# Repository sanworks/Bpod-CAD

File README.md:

# Bpod-CAD
CAD files for the Bpod behavior measurement system.
Bills of materials and build tips are given on the Bpod Wiki: https://sites.google.com/site/bpoddocumentation/home

(C) 2023 Sanworks LLC. These files are freely available under the terms of General Public License v3.0 (enclosed with this repository).

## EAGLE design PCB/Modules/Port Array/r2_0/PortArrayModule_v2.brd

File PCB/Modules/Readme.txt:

Note: With the exception of the 'For FSM r0.5' folder, modules in this folder are compatible with state machine r0.7 or newer.

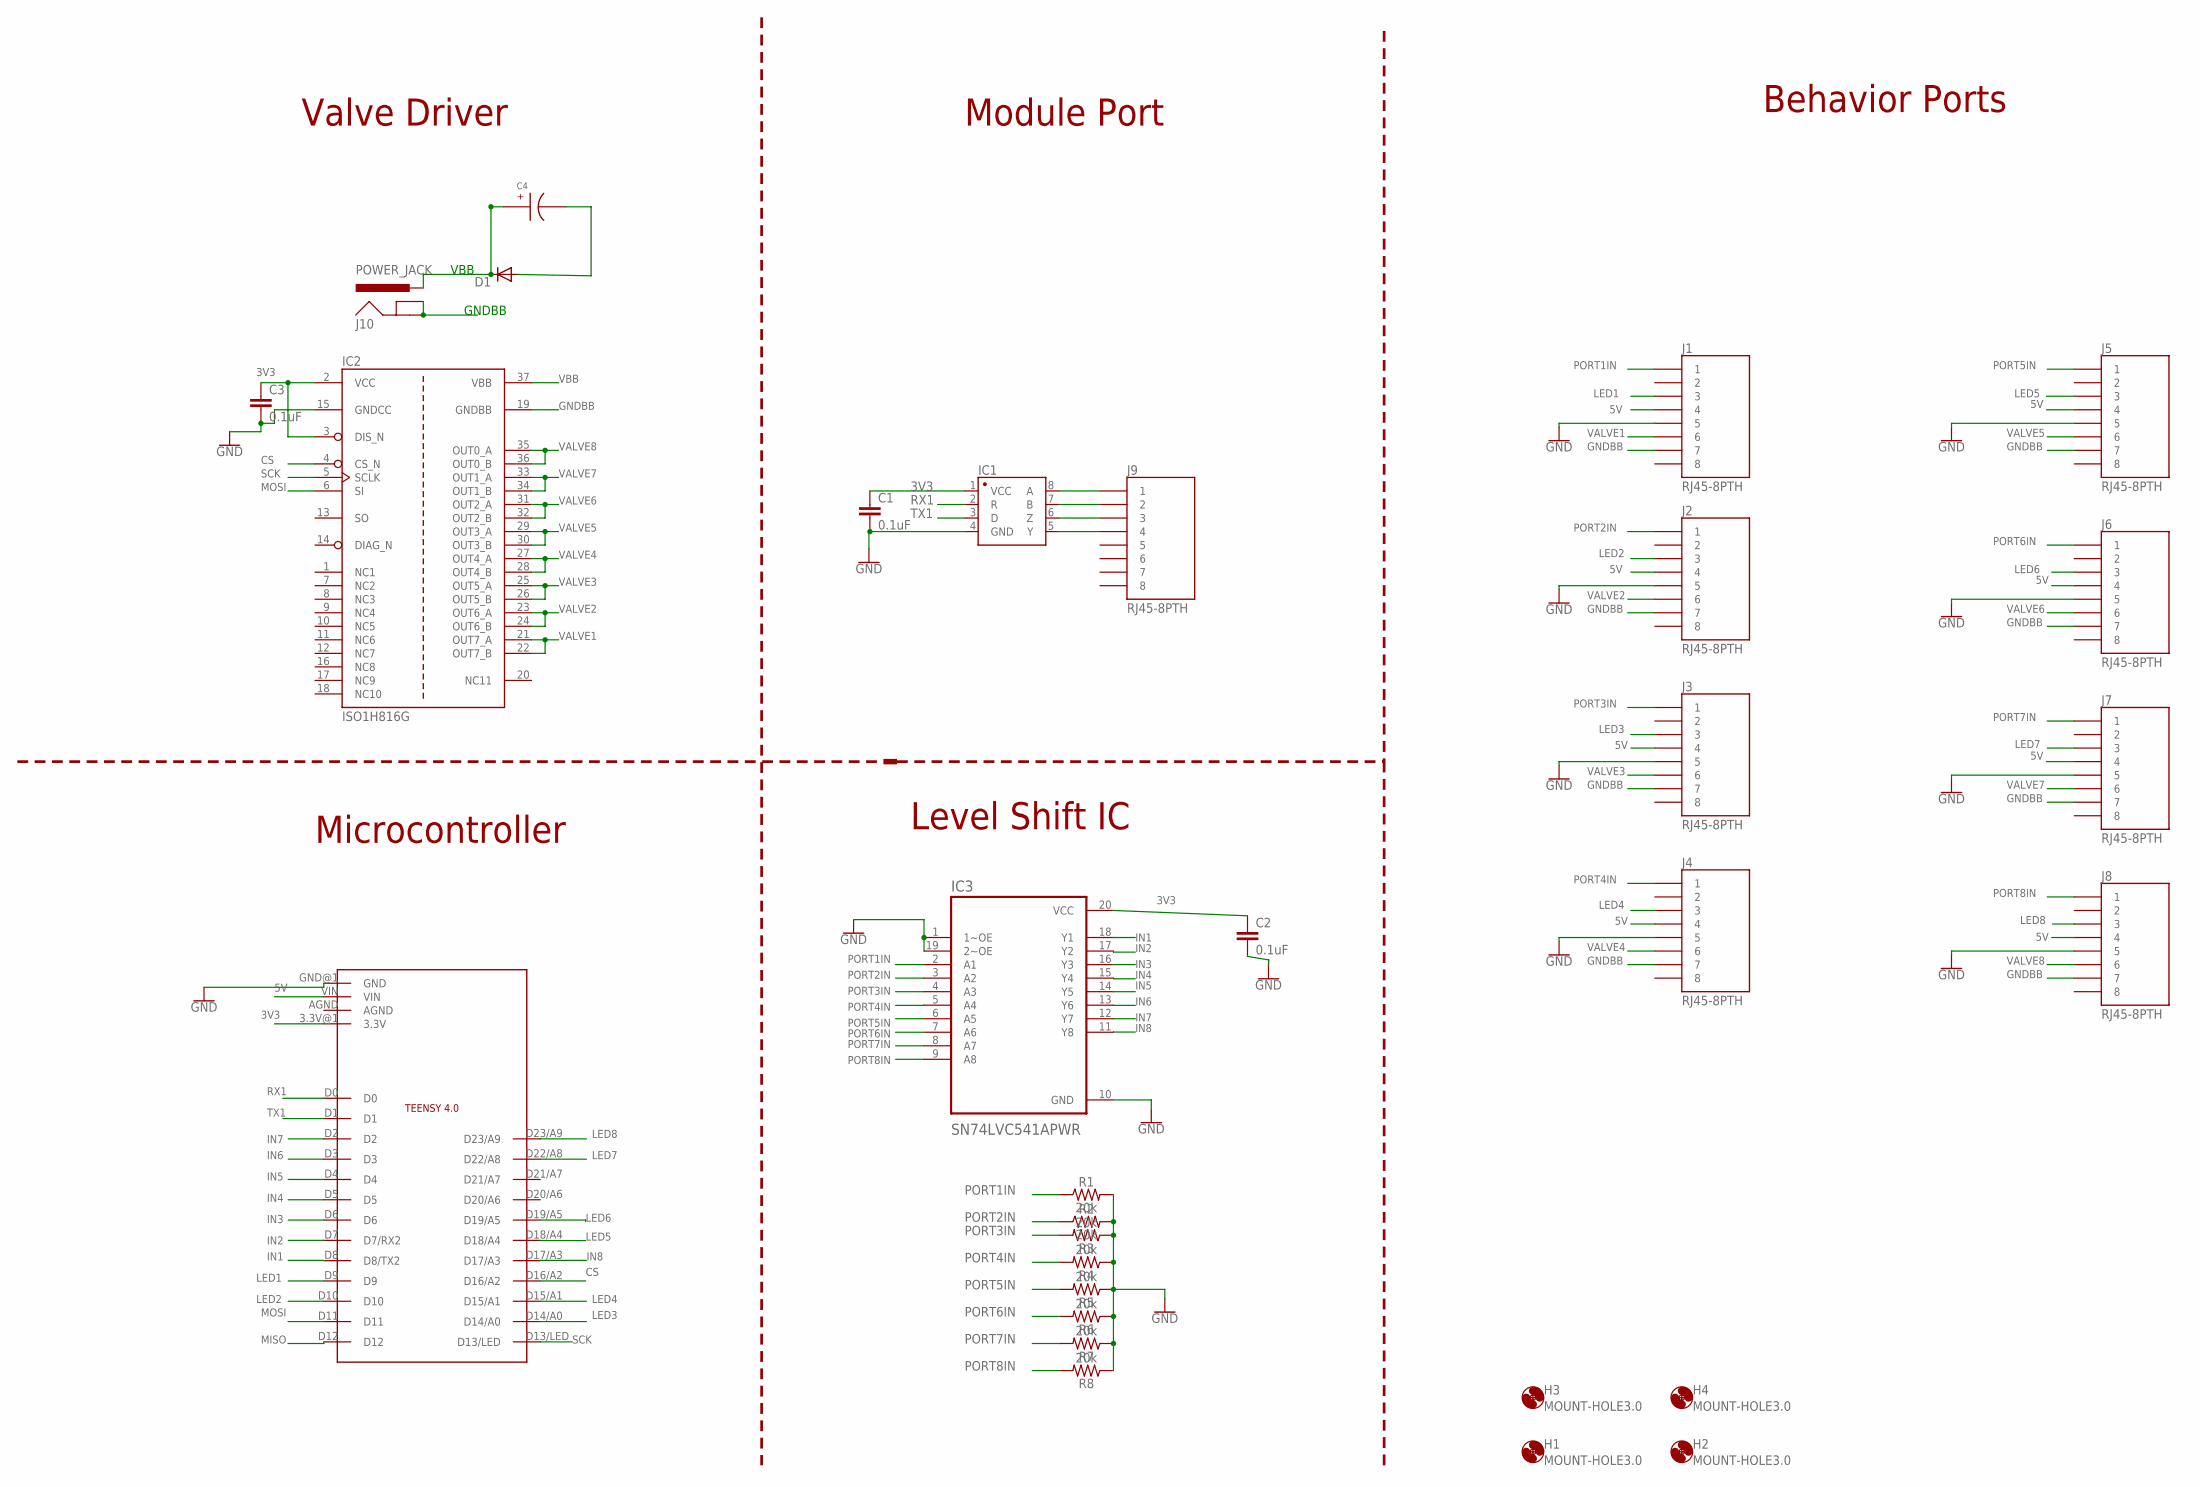
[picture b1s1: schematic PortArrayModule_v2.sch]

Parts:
C1, C2, C3: 0.1uF; 0805
C4: EEE-FK1H100UR
D1: DIODE-DO214AA; DO214AA
H1, H2, H3, H4: MOUNT-HOLE3.0; 3,0
IC1: SN65HVD31DR; SO08
IC2: ISO1H816G; SOP65P1420X350-37N-1-V
IC3: SN74LVC541APWR; SOP65P640X120-20N
J1, J2, J3, J4, J5, J6, J7, J8, J9: RJ45-8PTH; RJ45-8
J10: POWER_JACK; POWER_JACK_PTH
MC1: TEENSY4.0_SIMPLE_NO_VUSB
R1, R2, R3, R4, R5, R6, R7, R8: 20k; 0805

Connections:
3V3: C1.1, C2.1, C3.1, IC1.1 (VCC), IC2.2 (VCC), IC2.3 (DIS_N), IC3.20 (VCC), MC1.3.3V@1 (3.3V)
5V: J1.4, J2.4, J3.4, J4.4, J5.4, J6.4, J7.4, J8.4, MC1.VIN
CS: IC2.4 (CS_N), MC1.D16/A2
GND: C1.2, C2.2, C3.2, IC1.4 (GND), IC2.15 (GNDCC), IC3.1 (1~OE), IC3.10 (GND), IC3.19 (2~OE), J1.5, J2.5, J3.5, J4.5, J5.5, J6.5, J7.5, J8.5, MC1.GND@1 (GND), R1.2, R2.2, R3.1, R4.1, R5.1, R6.1, R7.1, R8.1
GNDBB: C4.CATHODE, D1.A, IC2.19 (GNDBB), J1.7, J2.7, J3.7, J4.7, J5.7, J6.7, J7.7, J8.7, J10.GND, J10.GNDBREAK
IN1: IC3.18 (Y1), MC1.D8 (D8/TX2)
IN2: IC3.17 (Y2), MC1.D7 (D7/RX2)
IN3: IC3.16 (Y3), MC1.D6
IN4: IC3.15 (Y4), MC1.D5
IN5: IC3.14 (Y5), MC1.D4
IN6: IC3.13 (Y6), MC1.D3
IN7: IC3.12 (Y7), MC1.D2
IN8: IC3.11 (Y8), MC1.D17/A3
LED1: J1.3, MC1.D9
LED2: J2.3, MC1.D10
LED3: J3.3, MC1.D14/A0
LED4: J4.3, MC1.D15/A1
LED5: J5.3, MC1.D18/A4
LED6: J6.3, MC1.D19/A5
LED7: J7.3, MC1.D22/A8
LED8: J8.3, MC1.D23/A9
MISO: MC1.D12
MOSI: IC2.6 (SI), MC1.D11
unnamed: IC1.6 (Z), J9.3
unnamed: IC1.5 (Y), J9.4
unnamed: IC1.8 (A), J9.1
unnamed: IC1.7 (B), J9.2
PORT1IN: IC3.2 (A1), J1.1, R1.1
PORT2IN: IC3.3 (A2), J2.1, R2.1
PORT3IN: IC3.4 (A3), J3.1, R3.2
PORT4IN: IC3.5 (A4), J4.1, R4.2
PORT5IN: IC3.6 (A5), J5.1, R5.2
PORT6IN: IC3.7 (A6), J6.1, R6.2
PORT7IN: IC3.8 (A7), J7.1, R7.2
PORT8IN: IC3.9 (A8), J8.1, R8.2
RX1: IC1.2 (R), MC1.D0
SCK: IC2.5 (SCLK), MC1.D13/LED
TX1: IC1.3 (D), MC1.D1
VALVE1: IC2.21 (OUT7_A), IC2.22 (OUT7_B), J1.6
VALVE2: IC2.23 (OUT6_A), IC2.24 (OUT6_B), J2.6
VALVE3: IC2.25 (OUT5_A), IC2.26 (OUT5_B), J3.6
VALVE4: IC2.27 (OUT4_A), IC2.28 (OUT4_B), J4.6
VALVE5: IC2.29 (OUT3_A), IC2.30 (OUT3_B), J5.6
VALVE6: IC2.31 (OUT2_A), IC2.32 (OUT2_B), J6.6
VALVE7: IC2.33 (OUT1_A), IC2.34 (OUT1_B), J7.6
VALVE8: IC2.35 (OUT0_A), IC2.36 (OUT0_B), J8.6
VBB: C4.ANODE, D1.C, IC2.37 (VBB), J10.PWR

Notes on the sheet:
VBB
GNDBB
Behavior Ports
Module Port
Valve Driver
Level Shift IC
Microcontroller

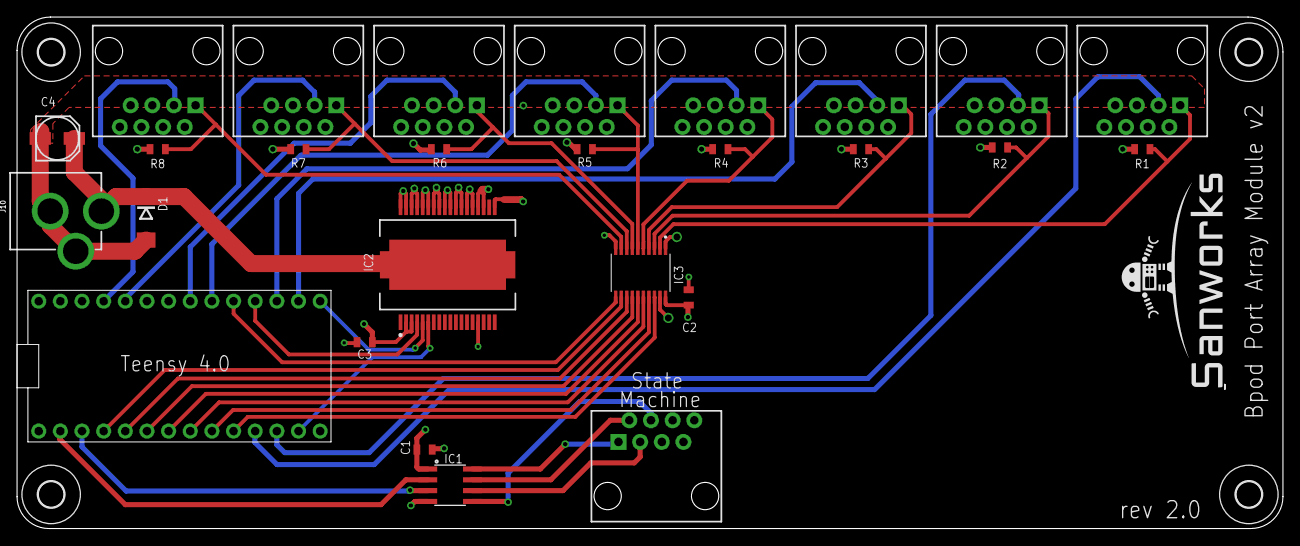
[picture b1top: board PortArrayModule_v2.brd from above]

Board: 4 copper layers, 148.5 x 60.0 mm, 32 parts (0 on the bottom side), 46 nets.

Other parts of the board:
U$1: SANWORKS_LOGO

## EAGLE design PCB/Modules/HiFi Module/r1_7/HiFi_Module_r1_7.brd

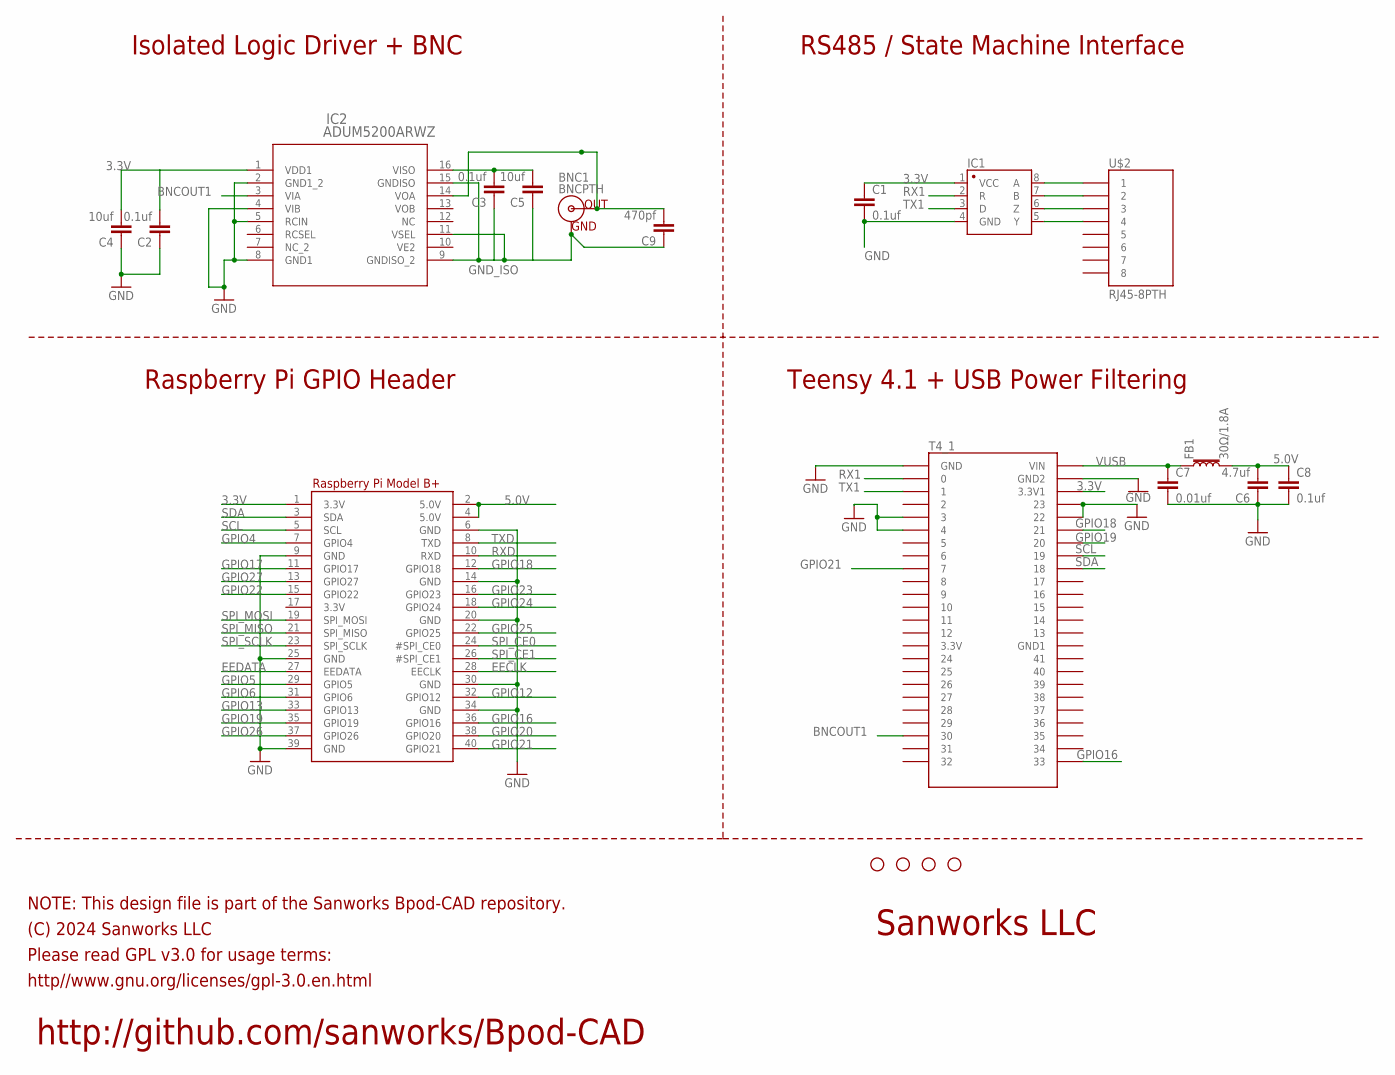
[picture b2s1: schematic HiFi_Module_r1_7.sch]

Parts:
BNC1: BNCPTH; BNC
C1, C2, C3, C8: 0.1uf; 0805
C4, C5: 10uf; 1206@2
C6: 4.7uf; 1206@2
C7: 0.01uf; 0805
C9: 470pf; 0805
FB1: 30Ω/1.8A; 0603
H1, H2, H3, H4: STAND-OFF
IC1: SN65HVD31DR; SO08
IC2: ADUM5200ARWZ; RW_16
RPI1: RASPBERRYPI_BPLUS_IDC; 2X20
T4_1: TEENSY4.1_SIDESONLY
U$2: RJ45-8PTH; RJ45-8

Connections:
3.3V: C1.1, C2.2, C4.2, IC1.1 (VCC), IC2.1 (VDD1), RPI1.1 (3.3V), T4_1.3V3_LO (3.3V1)
5.0V: C6.2, C8.1, FB1.2, RPI1.2 (5.0V), RPI1.4 (5.0V)
BNCOUT1: IC2.3 (VIA), T4_1.30
EECLK: RPI1.28 (EECLK)
EEDATA: RPI1.27 (EEDATA)
GND: C1.2, C2.1, C4.1, C6.1, C7.2, C8.2, IC1.4 (GND), IC2.2 (GND1_2), IC2.4 (VIB), IC2.5 (RCIN), IC2.8 (GND1), RPI1.6 (GND), RPI1.9 (GND), RPI1.14 (GND), RPI1.20 (GND), RPI1.25 (GND), RPI1.30 (GND), RPI1.34 (GND), RPI1.39 (GND), T4_1.3, T4_1.4, T4_1.22/A8 (22), T4_1.23/A9 (23), T4_1.AGND (GND), T4_1.GND1 (GND2)
GND_ISO: BNC1.GND, C3.1, C5.1, C9.1, IC2.9 (GNDISO_2), IC2.11 (VSEL), IC2.15 (GNDISO)
GPIO4: RPI1.7 (GPIO4)
GPIO5: RPI1.29 (GPIO5)
GPIO6: RPI1.31 (GPIO6)
GPIO12: RPI1.32 (GPIO12)
GPIO13: RPI1.33 (GPIO13)
GPIO16: RPI1.36 (GPIO16), T4_1.33
GPIO17: RPI1.11 (GPIO17)
GPIO18: RPI1.12 (GPIO18), T4_1.21/A7 (21)
GPIO19: RPI1.35 (GPIO19), T4_1.20/A6 (20)
GPIO20: RPI1.38 (GPIO20)
GPIO21: RPI1.40 (GPIO21), T4_1.7
GPIO22: RPI1.15 (GPIO22)
GPIO23: RPI1.16 (GPIO23)
GPIO24: RPI1.18 (GPIO24)
GPIO25: RPI1.22 (GPIO25)
GPIO26: RPI1.37 (GPIO26)
GPIO27: RPI1.13 (GPIO27)
unnamed: IC1.6 (Z), U$2.3
unnamed: IC1.8 (A), U$2.1
unnamed: IC1.5 (Y), U$2.4
unnamed: IC1.7 (B), U$2.2
unnamed: C3.2, C5.2, IC2.16 (VISO)
unnamed: BNC1.S (OUT), C9.2, IC2.14 (VOA)
RX1: IC1.2 (R), T4_1.0/RX (0)
RXD: RPI1.10 (RXD)
SCL: RPI1.5 (SCL), T4_1.19/A5/SCL (19)
SDA: RPI1.3 (SDA), T4_1.18/A4/SDA (18)
SPI_CE0: RPI1.24 (#SPI_CE0)
SPI_CE1: RPI1.26 (#SPI_CE1)
SPI_MISO: RPI1.21 (SPI_MISO)
SPI_MOSI: RPI1.19 (SPI_MOSI)
SPI_SCLK: RPI1.23 (SPI_SCLK)
TX1: IC1.3 (D), T4_1.1/TX (1)
TXD: RPI1.8 (TXD)
VUSB: C7.1, FB1.1, T4_1.VIN

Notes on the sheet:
http://github.com/sanworks/Bpod-CAD
NOTE: This design file is part of the Sanworks Bpod-CAD repository.
(C) 2024 Sanworks LLC
http//www.gnu.org/licenses/gpl-3.0.en.html
Please read GPL v3.0 for usage terms:
Sanworks LLC
Isolated Logic Driver + BNC
RS485 / State Machine Interface
Raspberry Pi GPIO Header
Teensy 4.1 + USB Power Filtering

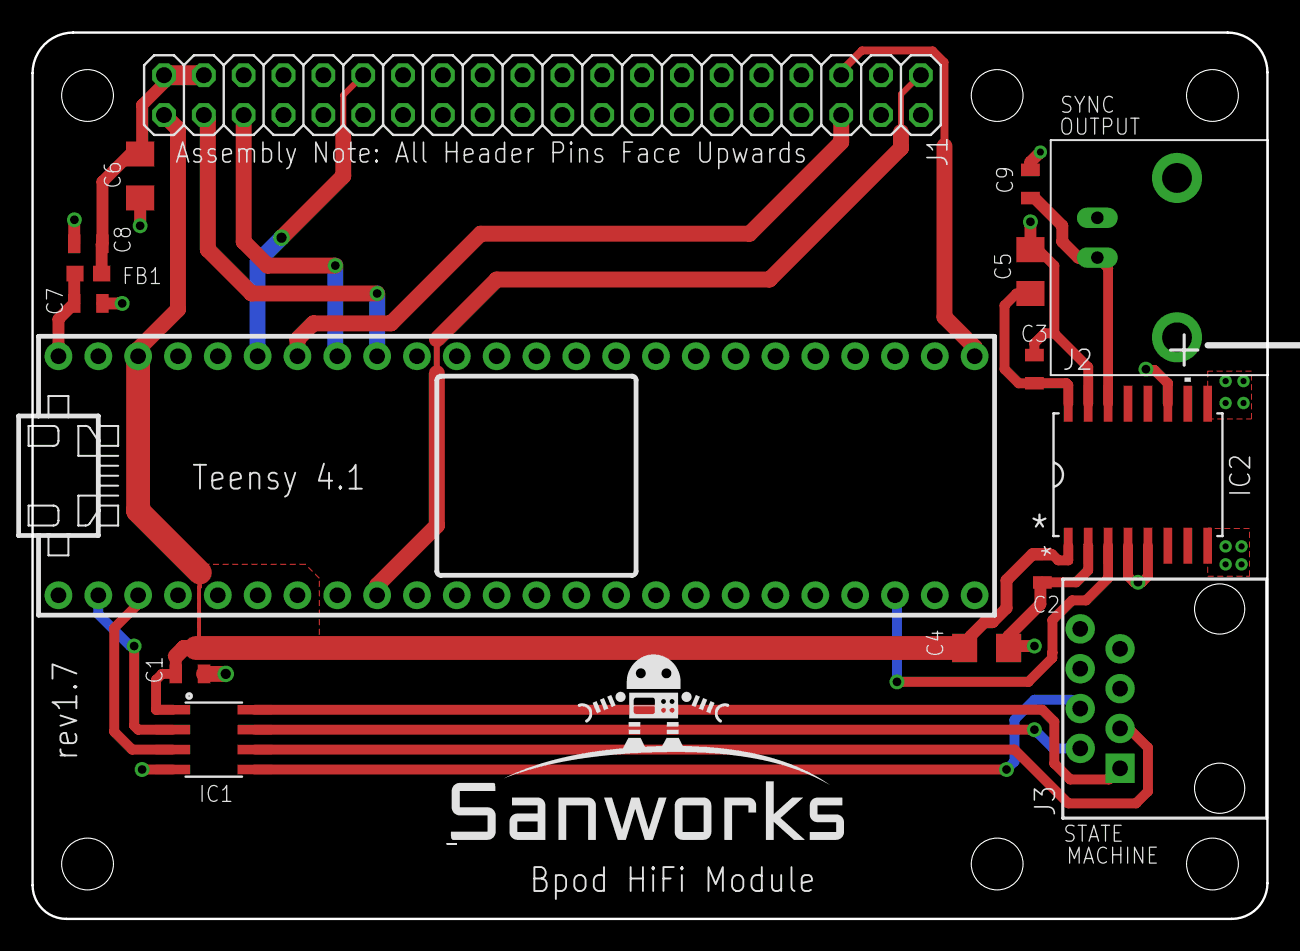
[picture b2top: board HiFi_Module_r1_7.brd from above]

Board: 2 copper layers, 78.7 x 56.5 mm, 23 parts (0 on the bottom side), 20 nets.

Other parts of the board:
H5, H6: STAND-OFF
U$1: SANWORKS_LOGO

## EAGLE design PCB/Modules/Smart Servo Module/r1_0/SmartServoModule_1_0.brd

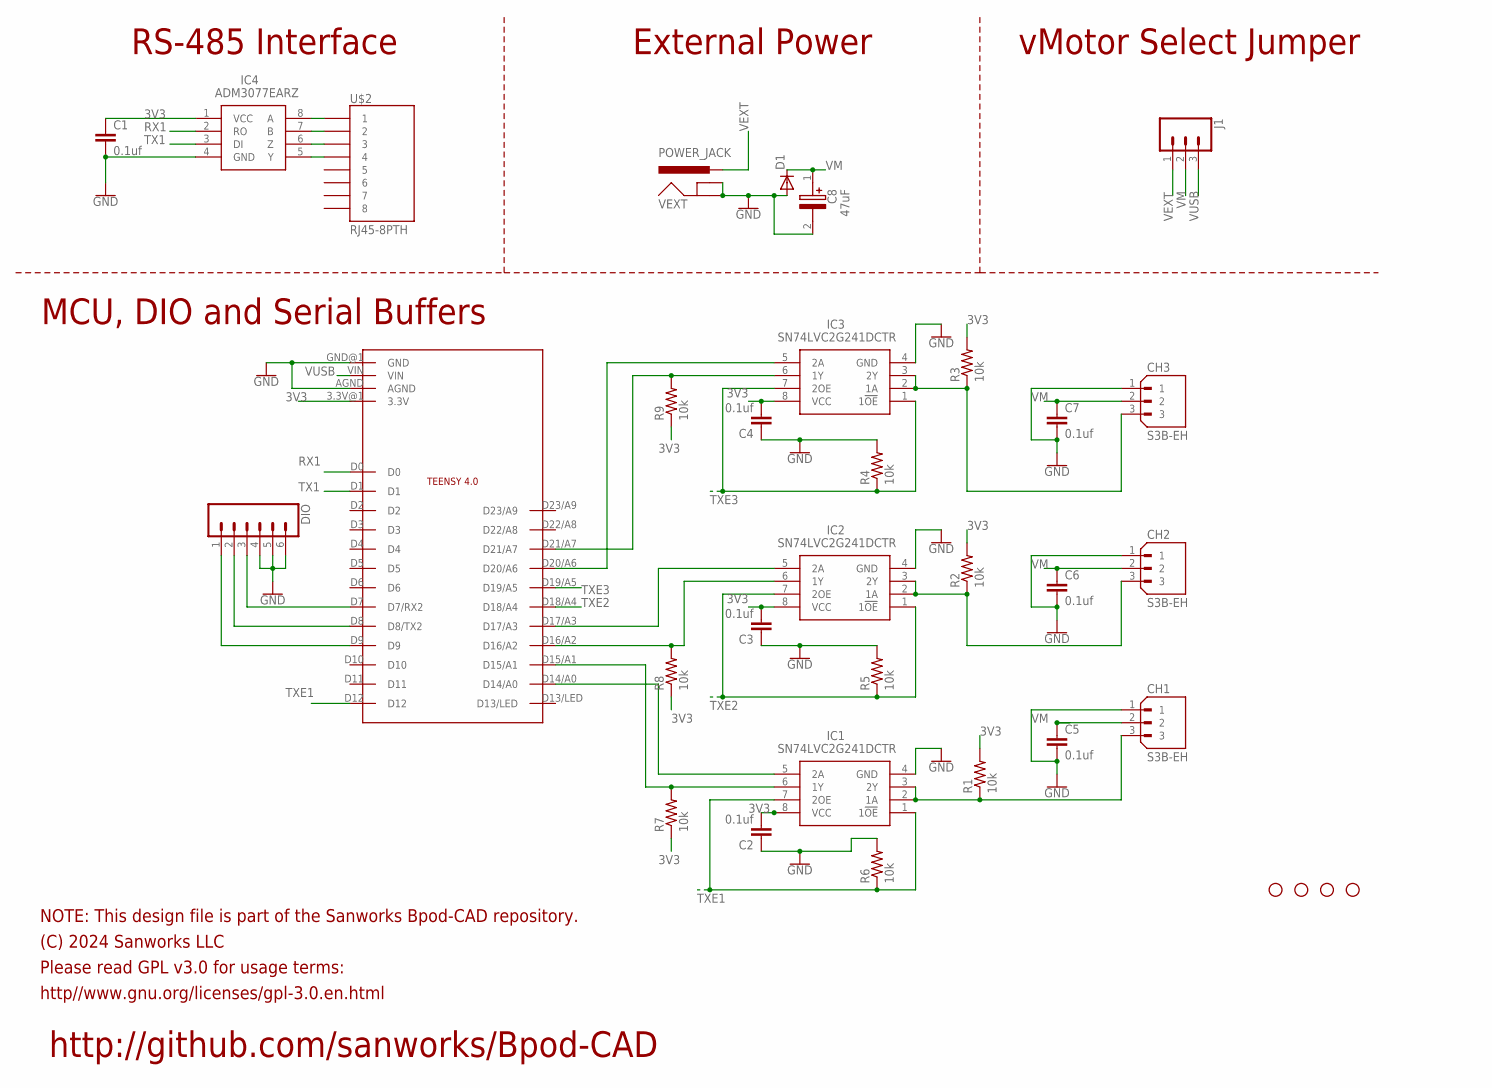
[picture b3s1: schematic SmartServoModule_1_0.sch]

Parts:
C1, C2, C3, C4, C5, C6, C7: 0.1uf; 0805
C8: 47uF; EEHZA1E101XP
CH1, CH2, CH3: S3B-EH; JST_S3B-EH
D1: DIODE-DO214AA; DO214AA
DIO: CONN_063.5MM-6; SCREWTERMINAL-3.5MM-6
H1, H2, H3, H4: STAND-OFF
IC1, IC2, IC3: SN74LVC2G241DCTR; SOP65P400X130-8N
IC4: ADM3077EARZ; SOIC127P600X175-8N
J1: CONN_03LOCK; 1X03_LOCK
MC1: TEENSY4.0_SIMPLE_NO_VUSB
R1, R2, R3, R4, R5, R6, R7, R8, R9: 10k; R0805
U$2: RJ45-8PTH; RJ45-8
VEXT: POWER_JACK; POWER_JACK_PTH

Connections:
3V3: C1.1, C2.2, C3.2, C4.2, IC1.8 (VCC), IC2.8 (VCC), IC3.8 (VCC), IC4.1 (VCC), MC1.3.3V@1 (3.3V), R1.2, R2.2, R3.2, R7.1, R8.1, R9.1
GND: C1.2, C2.1, C3.1, C4.1, C5.2, C6.2, C7.2, C8.2 (-), CH1.1, CH2.1, CH3.1, D1.A, DIO.4, DIO.5, DIO.6, IC1.4 (GND), IC2.4 (GND), IC3.4 (GND), IC4.4 (GND), MC1.AGND, MC1.GND@1 (GND), R4.2, R5.2, R6.2, VEXT.GND, VEXT.GNDBREAK
unnamed: IC4.6 (Z), U$2.3
unnamed: CH1.3, IC1.2 (1A), IC1.3 (2Y), R1.1
unnamed: IC4.8 (A), U$2.1
unnamed: IC4.5 (Y), U$2.4
unnamed: IC4.7 (B), U$2.2
unnamed: CH2.3, IC2.2 (1A), IC2.3 (2Y), R2.1
unnamed: CH3.3, IC3.2 (1A), IC3.3 (2Y), R3.1
unnamed: DIO.1, MC1.D9
unnamed: DIO.2, MC1.D8 (D8/TX2)
unnamed: DIO.3, MC1.D7 (D7/RX2)
unnamed: IC1.5 (2A), MC1.D14/A0
unnamed: IC1.6 (1Y), MC1.D15/A1, R7.2
unnamed: IC2.5 (2A), MC1.D17/A3
unnamed: IC2.6 (1Y), MC1.D16/A2, R8.2
unnamed: IC3.5 (2A), MC1.D20/A6
unnamed: IC3.6 (1Y), MC1.D21/A7, R9.2
RX1: IC4.2 (RO), MC1.D0
TX1: IC4.3 (DI), MC1.D1
TXE1: IC1.1 (1!OE), IC1.7 (2OE), MC1.D12, R6.1
TXE2: IC2.1 (1!OE), IC2.7 (2OE), MC1.D18/A4, R5.1
TXE3: IC3.1 (1!OE), IC3.7 (2OE), MC1.D19/A5, R4.1
VEXT: J1.1, VEXT.PWR
VM: C5.1, C6.1, C7.1, C8.1 (+), CH1.2, CH2.2, CH3.2, D1.C, J1.2
VUSB: J1.3, MC1.VIN

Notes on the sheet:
RS-485 Interface
External Power
vMotor Select Jumper
MCU, DIO and Serial Buffers
http://github.com/sanworks/Bpod-CAD
NOTE: This design file is part of the Sanworks Bpod-CAD repository.
(C) 2024 Sanworks LLC
http//www.gnu.org/licenses/gpl-3.0.en.html
Please read GPL v3.0 for usage terms:

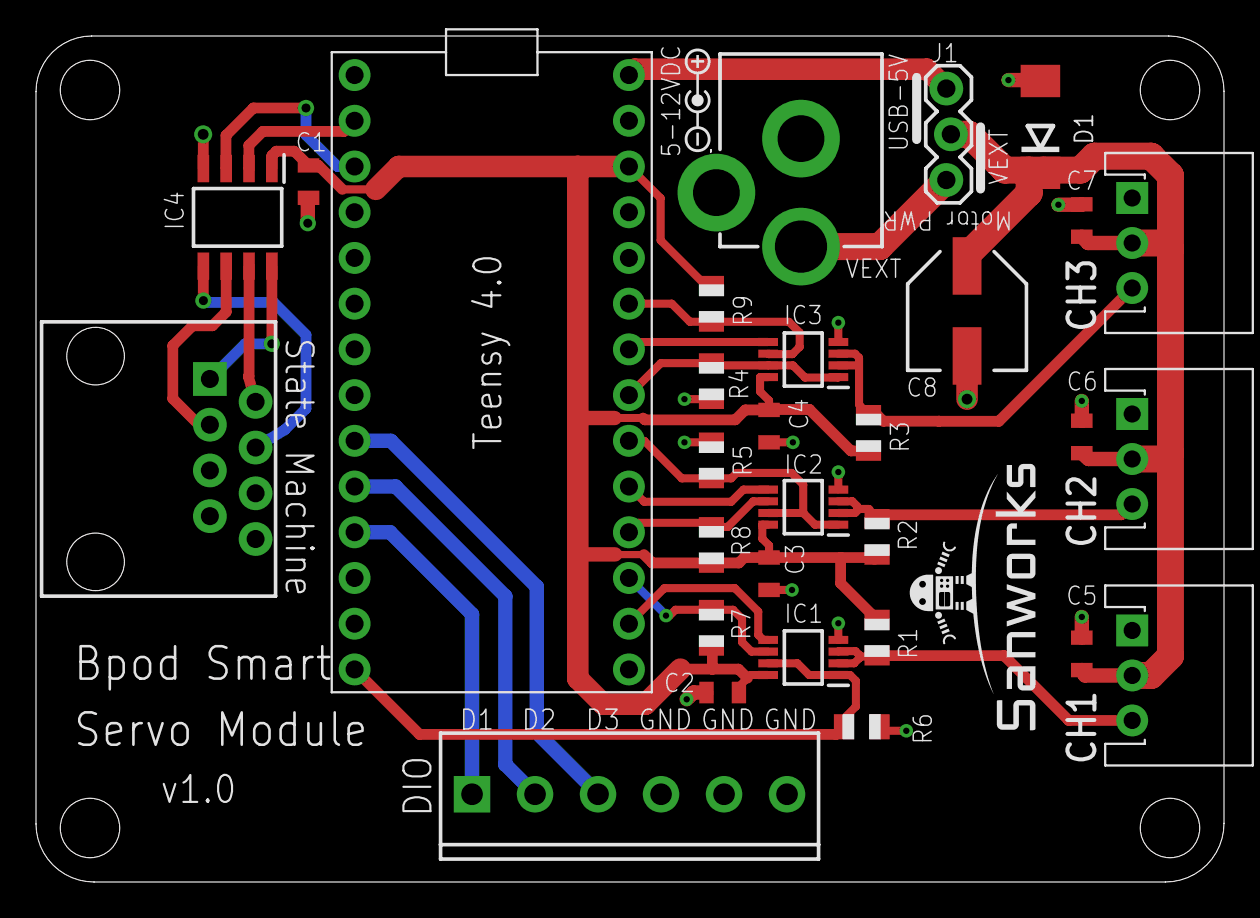
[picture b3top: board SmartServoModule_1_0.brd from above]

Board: 2 copper layers, 66.0 x 47.0 mm, 36 parts (0 on the bottom side), 26 nets.

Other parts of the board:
U$1: SANWORKS_LOGO_SM
U$3: POS-CTR-SYMBOL

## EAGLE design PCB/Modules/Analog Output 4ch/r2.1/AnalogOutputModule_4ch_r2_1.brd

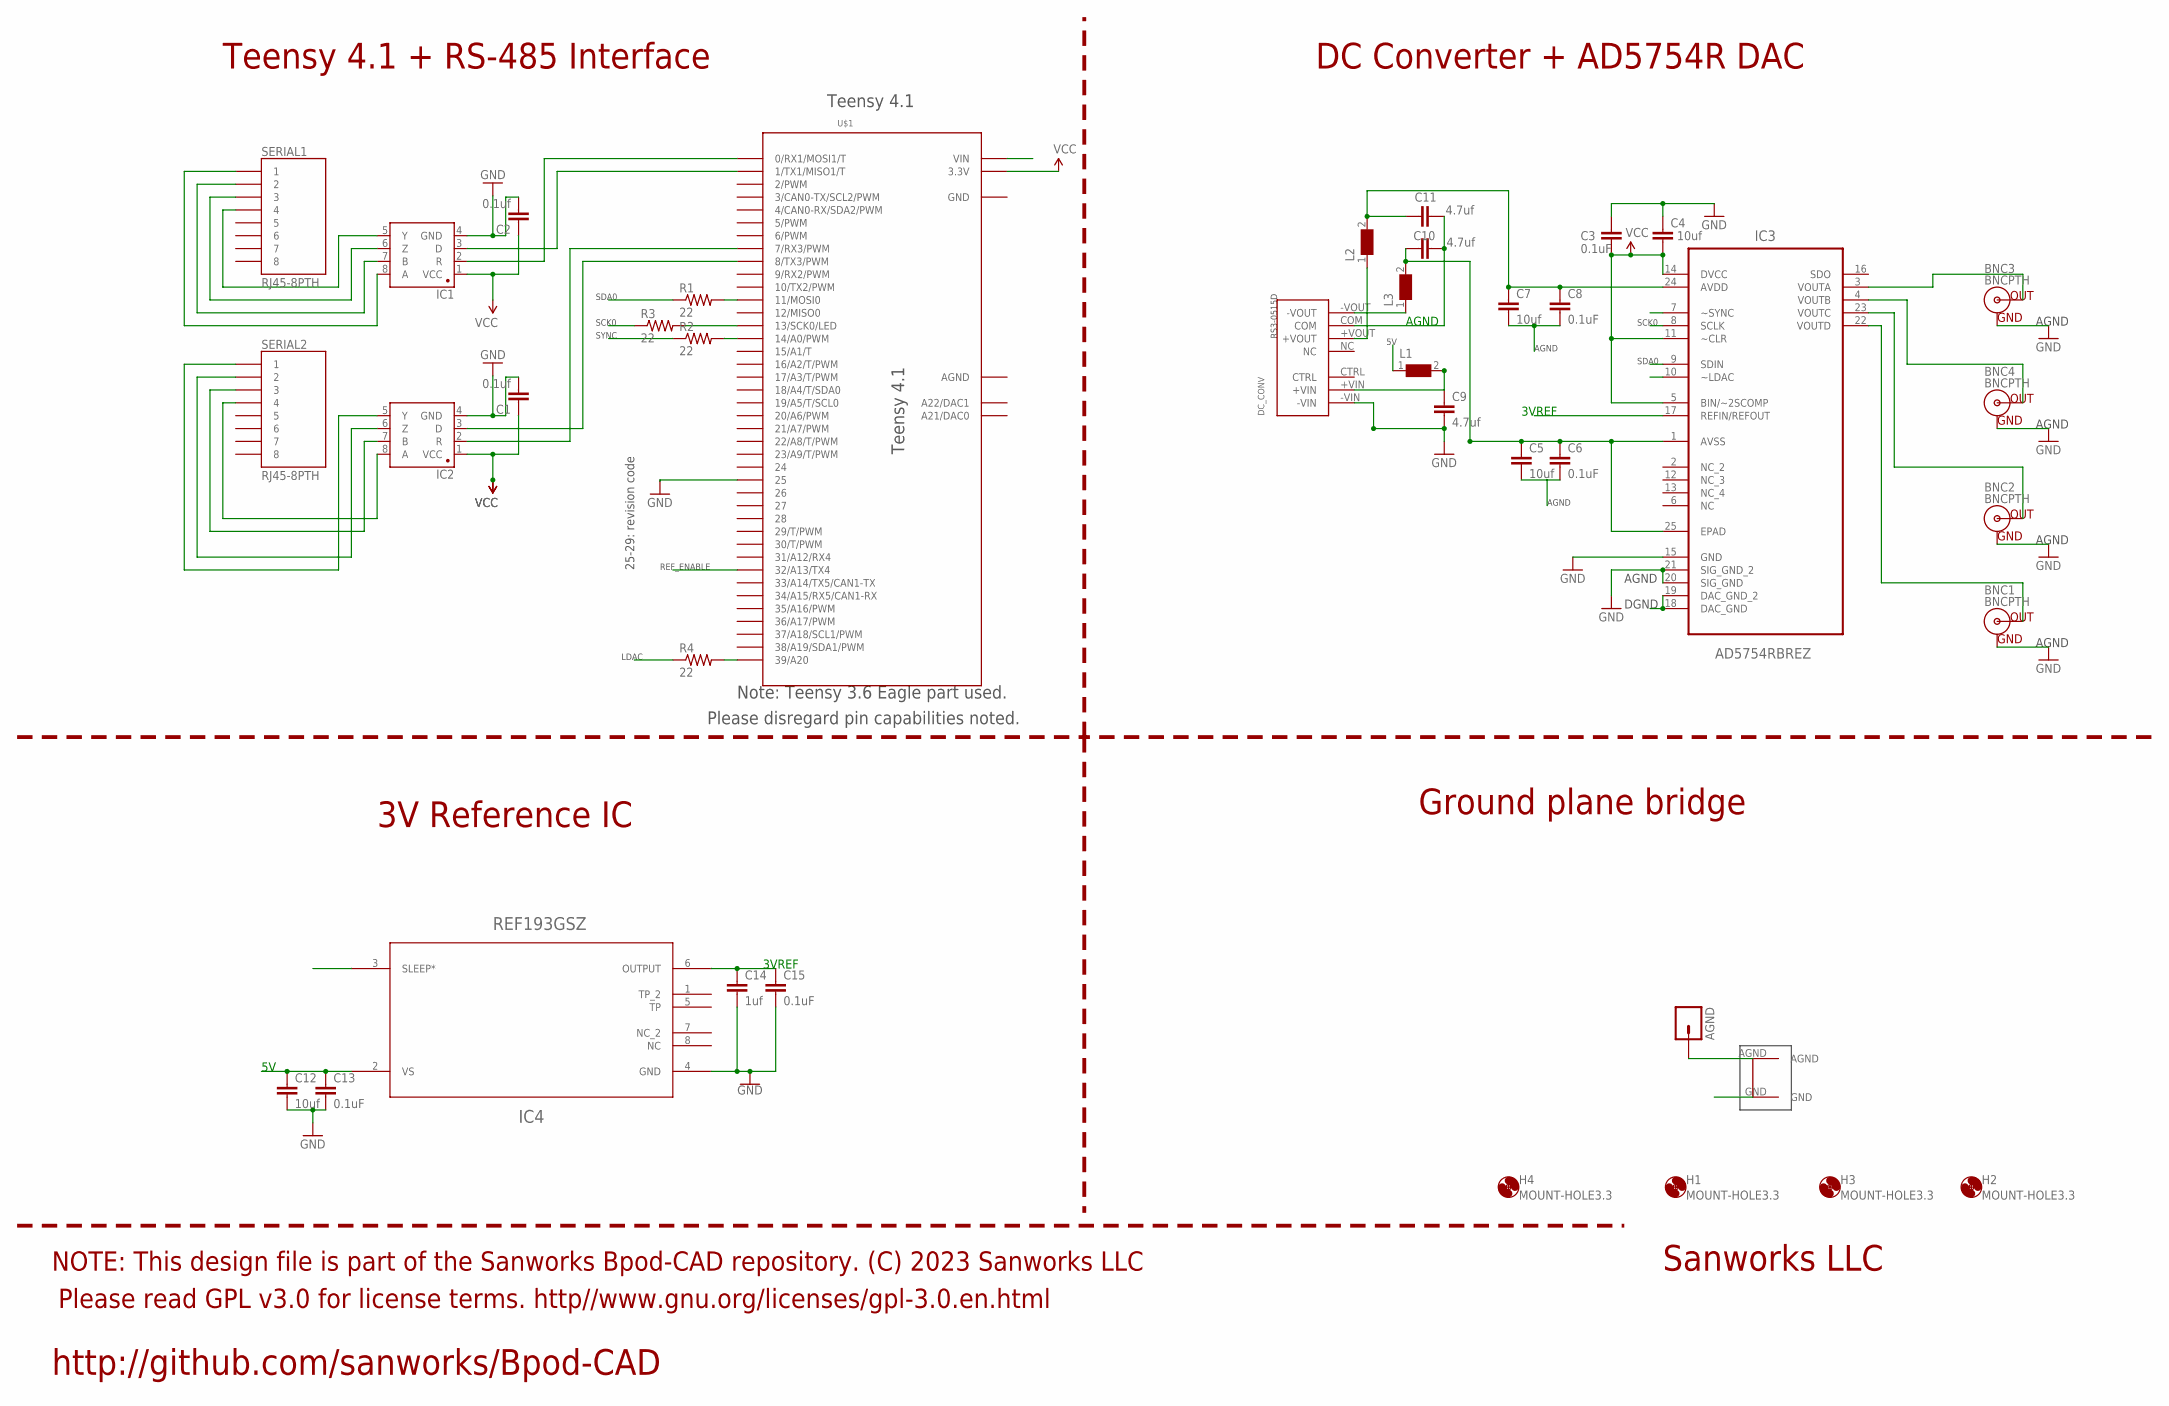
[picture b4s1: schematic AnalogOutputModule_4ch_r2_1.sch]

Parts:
AGND: M01PTH; 1X01
BNC1, BNC2, BNC3, BNC4: BNCPTH; BNC
C1, C2: 0.1uf; 1206@1
C3, C6, C8, C13, C15: 0.1uF; 0805
C4, C5, C7, C12: 10uf; 1206@1
C9, C10, C11: 4.7uf; 1206@1
C14: 1uf; 1206@1
DC_CONV: RS3-0515D
H1, H2, H3, H4: MOUNT-HOLE3.3; 3,3
IC1, IC2: SN65HVD31DR; SO08
IC3: AD5754RBREZ; SOP65P640X120-25N
IC4: REF193GSZ; R_8
L1, L2, L3: WE-CBF-742792118_1206; 1206
R1, R2, R3, R4: 22; 1206
SERIAL1, SERIAL2: RJ45-8PTH; RJ45-8
U$1: TEENSY_3.6_DIL
U$6: GNDPLANESHRT

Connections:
3VREF: C14.1, C15.1, IC3.17 (REFIN/REFOUT), IC4.6 (OUTPUT)
5V: C3.2, C4.2, C12.1, C13.1, IC3.5 (BIN/~2SCOMP), IC3.11 (~CLR), IC3.14 (DVCC), IC4.2 (VS), L1.1, U$1.VIN
AGND: AGND.1, BNC1.GND, BNC2.GND, BNC3.GND, BNC4.GND, C5.2, C6.2, C7.2, C8.2, C10.1, C11.2, DC_CONV.COM, IC3.18 (DAC_GND), IC3.19 (DAC_GND_2), IC3.20 (SIG_GND), IC3.21 (SIG_GND_2), U$1.AGND, U$6.AGND
GND: C1.2, C2.2, C3.1, C4.1, C9.2, C12.2, C13.2, C14.2, C15.2, DC_CONV.-VIN, IC1.4 (GND), IC2.4 (GND), IC3.15 (GND), IC4.4 (GND), U$1.25, U$1.GND, U$1.GND1 (GND), U$6.GND
LDAC: IC3.10 (~LDAC), R4.1
unnamed: IC1.3 (D), U$1.1 (1/TX1/MISO1/T)
unnamed: IC1.2 (R), U$1.0 (0/RX1/MOSI1/T)
unnamed: IC2.8 (A), SERIAL2.4
unnamed: IC2.7 (B), SERIAL2.3
unnamed: IC2.6 (Z), SERIAL2.2
unnamed: IC2.5 (Y), SERIAL2.1
unnamed: IC2.3 (D), U$1.8 (8/TX3/PWM)
unnamed: IC2.2 (R), U$1.7 (7/RX3/PWM)
unnamed: BNC3.S (OUT), IC3.3 (VOUTA)
unnamed: BNC4.S (OUT), IC3.4 (VOUTB)
unnamed: BNC2.S (OUT), IC3.23 (VOUTC)
unnamed: BNC1.S (OUT), IC3.22 (VOUTD)
unnamed: R1.2, U$1.11 (11/MOSI0)
unnamed: R3.2, U$1.13 (13/SCK0/LED)
unnamed: DC_CONV.-VOUT, L3.1
unnamed: DC_CONV.+VOUT, L2.1
unnamed: R2.2, U$1.14/A0 (14/A0/PWM)
unnamed: R4.2, U$1.39/A20
unnamed: IC1.8 (A), SERIAL1.1
unnamed: IC1.7 (B), SERIAL1.2
unnamed: IC1.6 (Z), SERIAL1.3
unnamed: IC1.5 (Y), SERIAL1.4
unnamed: C7.1, C8.1, C10.2, IC3.24 (AVDD), L2.2
unnamed: C9.1, DC_CONV.+VIN, L1.2
REF_ENABLE: IC4.3 (SLEEP*), U$1.32/A13 (32/A13/TX4)
SCK0: IC3.8 (SCLK), R3.1
SDA0: IC3.9 (SDIN), R1.1
SYNC: IC3.7 (~SYNC), R2.1
VCC: C1.1, C2.1, IC1.1 (VCC), IC2.1 (VCC), U$1.3.3V, U$1.3.3V3 (3.3V)
VSS: C5.1, C6.1, C11.1, IC3.1 (AVSS), IC3.25 (EPAD), L3.2

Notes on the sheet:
AGND
SCK0
SDA0
DGND
SYNC
LDAC
3VREF
REF_ENABLE
Teensy 4.1 + RS-485 Interface
DC Converter + AD5754R DAC
3V Reference IC
Ground plane bridge
Please read GPL v3.0 for license terms. http//www.gnu.org/licenses/gpl-3.0.en.html
NOTE: This design file is part of the Sanworks Bpod-CAD repository. (C) 2023 Sanworks LLC
Sanworks LLC
http://github.com/sanworks/Bpod-CAD
Teensy 4.1
Note: Teensy 3.6 Eagle part used.
Please disregard pin capabilities noted.
25-29: revision code

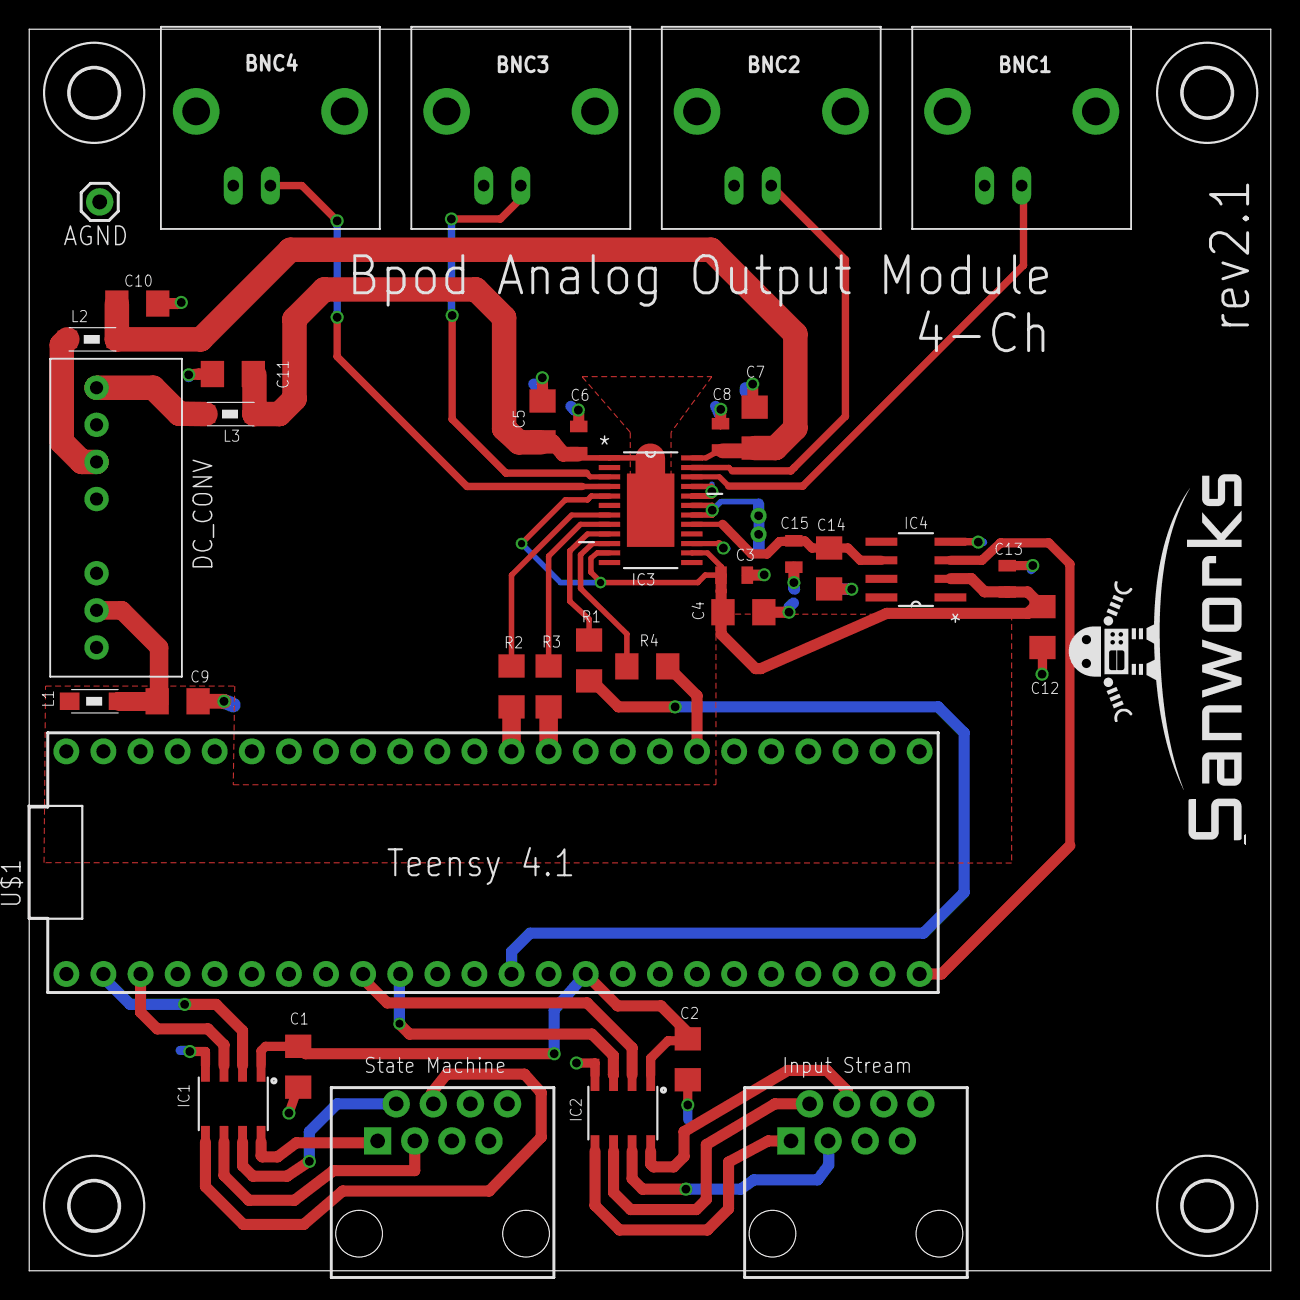
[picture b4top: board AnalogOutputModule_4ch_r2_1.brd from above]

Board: 2 copper layers, 85.0 x 85.0 mm, 41 parts (0 on the bottom side), 35 nets.

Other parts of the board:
U$2: SANWORKS_LOGO

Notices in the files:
parts and their libraries:
SparkFun-Capacitors: Licensing: Creative Commons ShareAlike 4.0 International - https://creativecommons.org/licenses/by-sa/4.0
SparkFun-Passives: Licensing: CC v3.0 Share-Alike You are welcome to use this library for commercial purposes.
